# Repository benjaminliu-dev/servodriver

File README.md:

# servodriver

ServoDriver is a 3-servo easy-to-use servo driver board. It operates over UART. 

I made ServoDriver because I wanted to not only introduce myself to the robotics utility field but also to create a useful servo driver solution that can be controlled via a laptop or SBC. I also made this to learn how to make a PCB without a dev board.

### Bill Of Materials

|Name|Link|   Cost |
| :------------ | :-----------: |-------:|
|        ATTiny412| https://www.digikey.com/en/products/detail/microchip-technology/ATTINY412-SSF/9947539          |  $0.55 |
|      3 x 3-Pin JST |         https://www.digikey.com/en/products/detail/jst-sales-america-inc/B3B-EH-A/926521 | $0.39 |
|     5-Pin Header    |       https://www.digikey.com/en/products/detail/oupiin/2011-1X05G00SB/12148491      | $0.50 |

### Total Pre-Tax Cost: $1.18

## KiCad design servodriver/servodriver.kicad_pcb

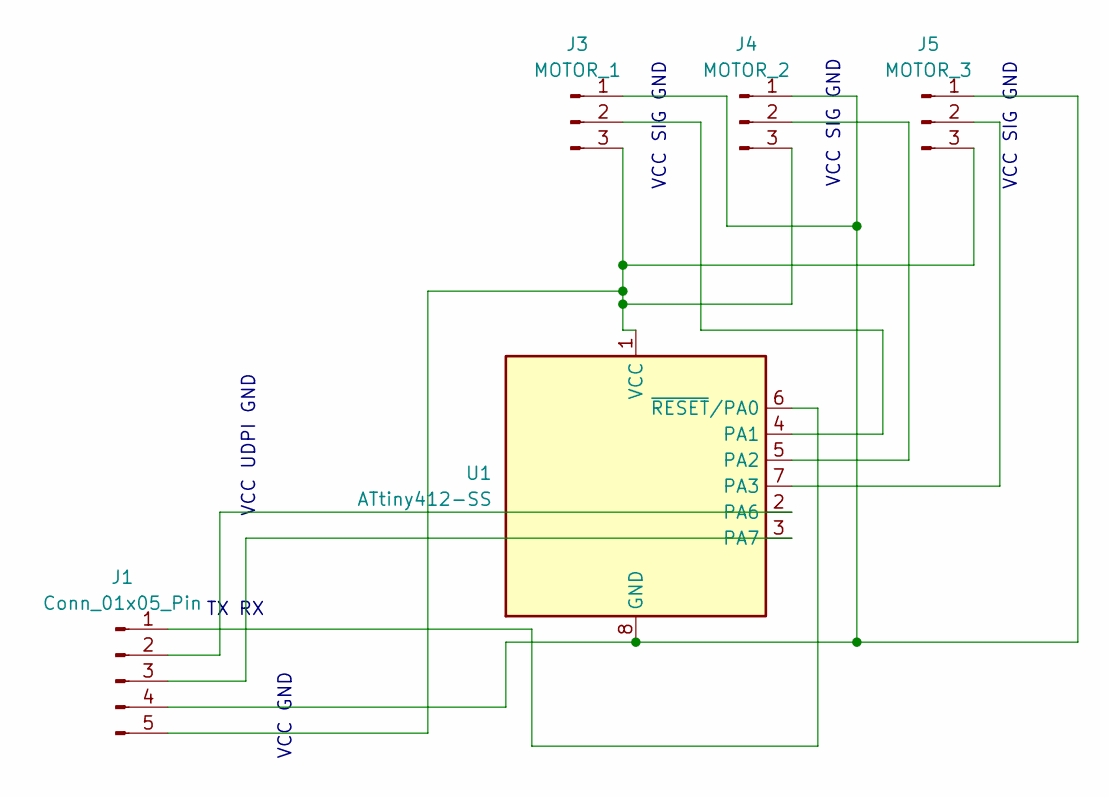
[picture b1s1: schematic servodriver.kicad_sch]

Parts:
J1: Conn_01x05_Pin; PinHeader_1x05_P1.27mm_Vertical
J3: MOTOR_1; JST_EH_B3B-EH-A_1x03_P2.50mm_Vertical
J4: MOTOR_2; JST_EH_B3B-EH-A_1x03_P2.50mm_Vertical
J5: MOTOR_3; JST_EH_B3B-EH-A_1x03_P2.50mm_Vertical
U1: ATtiny412-SS; SOIC-8_3.9x4.9mm_P1.27mm

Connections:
unnamed: J1.1, U1.6 (~RESET/PA0)
unnamed: J1.2, U1.2 (PA6)
unnamed: J1.3, U1.3 (PA7)
unnamed: J1.4, J3.1, J4.1, J5.1, U1.8 (GND)
unnamed: J1.5, J3.3, J4.3, J5.3, U1.1 (VCC)
unnamed: J3.2, U1.4 (PA1)
unnamed: J4.2, U1.5 (PA2)
unnamed: J5.2, U1.7 (PA3)

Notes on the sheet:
VCC GND
VCC SIG GND
TX RX
VCC UDPI GND

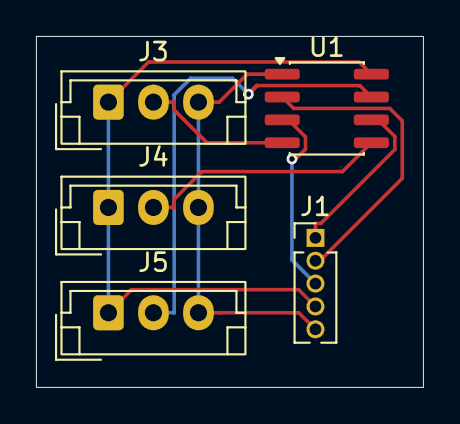
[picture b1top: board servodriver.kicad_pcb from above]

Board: 2 copper layers, 21.5 x 19.5 mm, 5 parts (0 on the bottom side), 8 nets.

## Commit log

2026-03-31 init
2026-03-31 replace zip
2026-03-31 servodriver
2026-03-31 optimization
